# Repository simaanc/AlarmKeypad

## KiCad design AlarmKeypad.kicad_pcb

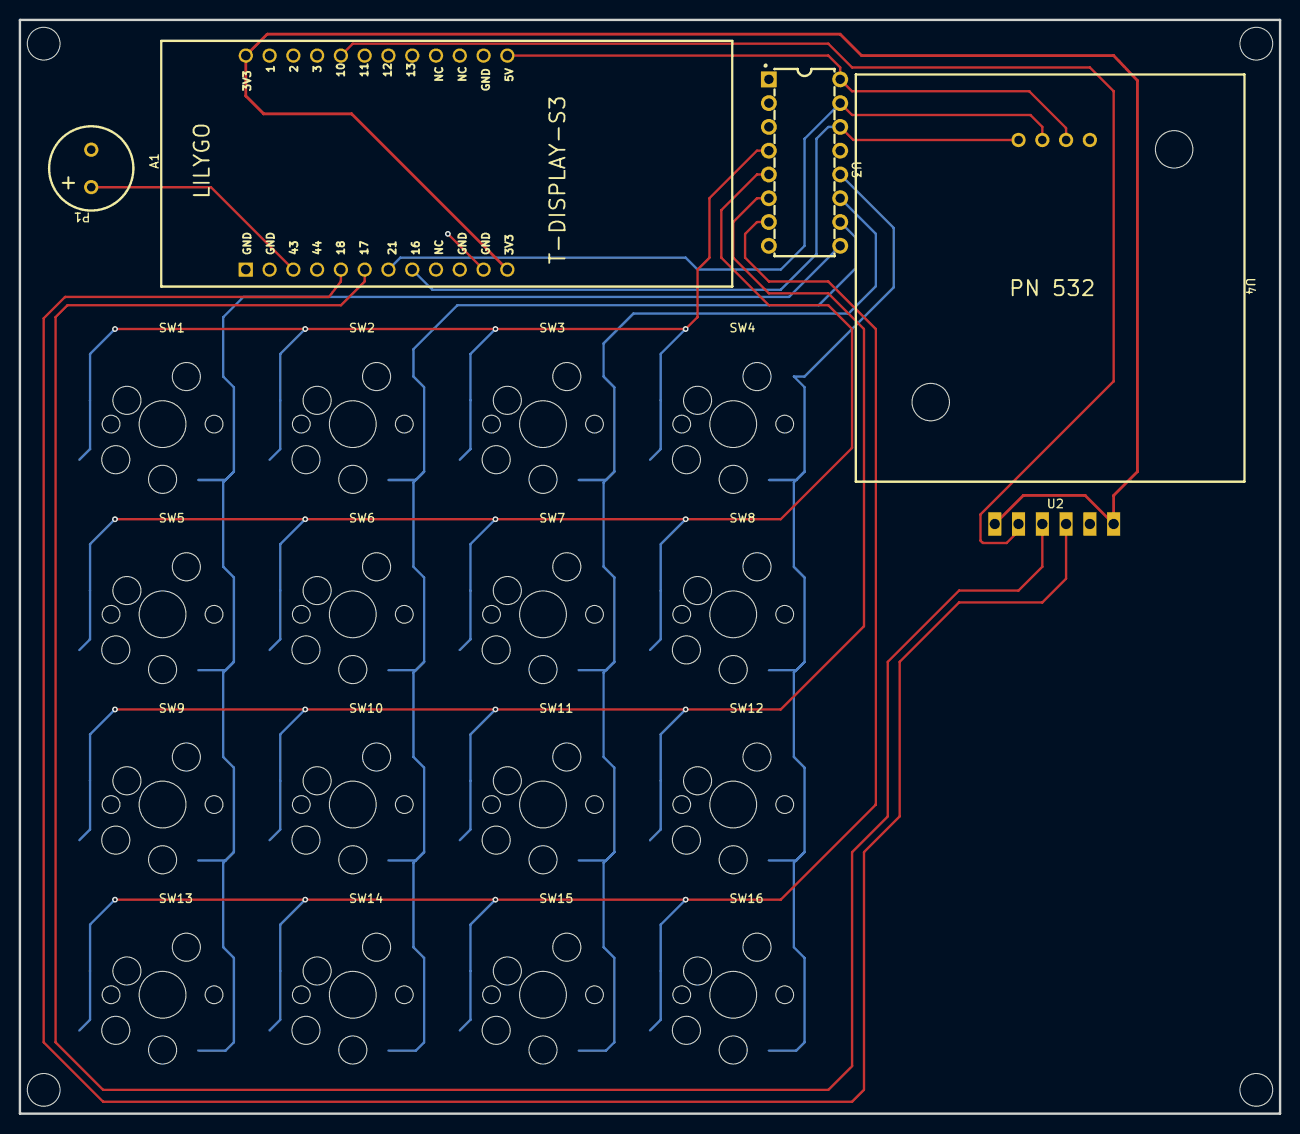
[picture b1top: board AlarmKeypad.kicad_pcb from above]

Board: 2 copper layers, 134.6 x 116.8 mm, 25 parts (0 on the bottom side), 17 nets.

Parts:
A1: myTTGO T-DISPLAY-S3 -NO_CUTOUT; TTGO T-DISPLAY-S3 AFS
Hole_gge39394: Hole_gge39394
Hole_gge39424: Hole_gge39424
Hole_gge39439: Hole_gge39439
Hole_gge39454: Hole_gge39454
P1: 9X9MM_SMD_PIEZO MURATA; PIEZO_9MM_TH
SW1, SW2, SW3, SW4, SW5, SW6, SW7, SW8, SW9, SW10, SW11, SW12, SW13, SW14, SW15, SW16: KAILH MX; KAILH MX CHOC V1 CHOC V2 HOT SWAP
U2: R503; R503 FINGERPRINT READER
U3: PCF8574AN; PDIP-16_L19.7-W6.6-P2.54-LS7.6-BL
U4: PN532MOD COPY; PN532MOD

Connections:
3V3: A1.12, A1.24, U2.1, U2.6
C1: SW1.2, SW5.2, SW9.2, SW13.2, U3.9
C2: SW2.2, SW6.2, SW10.2, SW14.2, U3.10
C3: SW3.2, SW7.2, SW11.2, SW15.2, U3.11
C4: SW4.2, SW8.2, SW12.2, SW16.2, U3.12
GND: A1.11, P1.2, U2.2, U3.1, U3.2, U3.3, U3.8, U4.1
GPIO43: A1.3, P1.1
R1: SW1.1, SW2.1, SW3.1, SW4.1, U3.4
R2: SW5.1, SW6.1, SW7.1, SW8.1, U3.5
R3: SW9.1, SW10.1, SW11.1, SW12.1, U3.6
R4: SW13.1, SW14.1, SW15.1, SW16.1, U3.7
RXD: A1.6, U2.4
SCL: A1.8, U3.14, U4.4
SDA: A1.7, U3.15, U4.3
TXD: A1.5, U2.3
VCC: A1.13, U3.16, U4.2
WAKEUP: A1.20, U2.5

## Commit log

2024-05-15 Initial Migration
2024-05-15 Updated File Names
2024-05-15 Update Git Ignore
2024-05-15 Update gitignore
